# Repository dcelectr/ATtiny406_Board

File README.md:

# ATtiny406_Board
PCB Design Files for ATtiny406 Board

This board design is a variant of a board design that is found in the blog link below.

https://www.omzlo.com/articles/baremetal-programming-on-the-tinyavr-0-micro-controllers

The board features fairly easy to hand solder components, such as a SOIC20 IC and 0805 resistors, capacitors and LEDs, and it is breadboard friendly (100 mil spacing pin headers) with an orderly pin arrangement (PA0->PA7, PB0->PB5, and PC0->PC3). 

The programming connector is a standard FTDI USB-UART adapter pin-out. Since most FTDI USB-UART cables have different voltage for the Vcc and Vttl (such as the TTL-232R-3V3), a solder jumper (JP1) is open by default. The board can be powered from the breadboard pin headers or the FTDI programming header if the the jumper JP1 is closed. Using an FTDI TTL-232RG-VIP USB-UART requires the jumper JP1 to be closed so that the TTL-232RG-VIP adapter TTL voltage (Vttl) would be the same as the Vcc.

The Bill of Materials is also included (see file ATtiny406BOM.csv).

Resistance of 4k7 Ohms works reliably for programming the Attiny406 over the range of Vcc, from 5V to 3V3.

Programming was tested on Linux with updiprog https://github.com/DCelectronics/updiprog (which is written in C) instead of using pyupdi.

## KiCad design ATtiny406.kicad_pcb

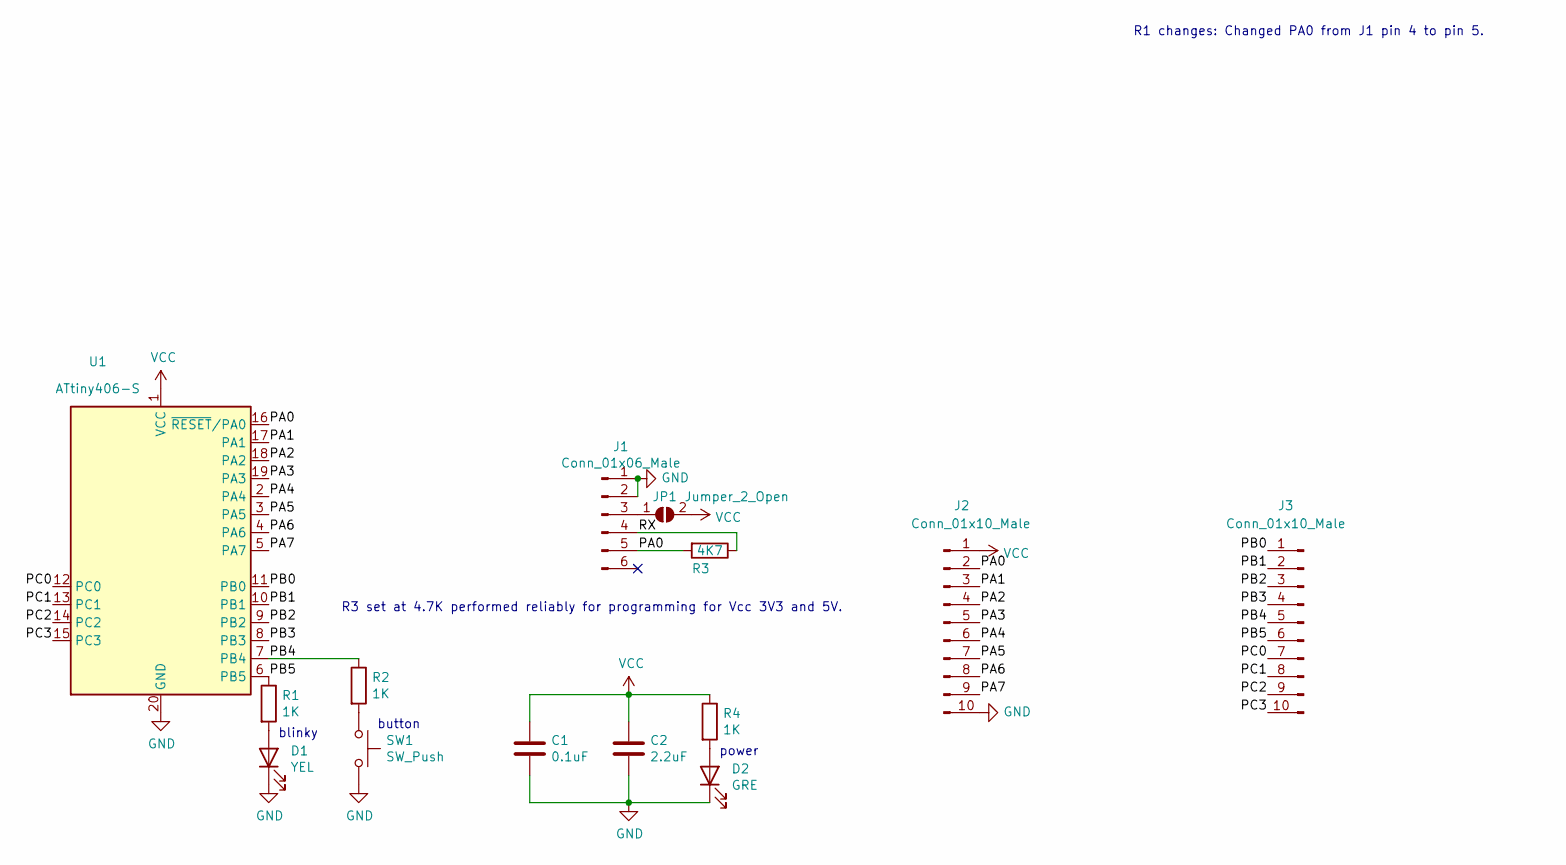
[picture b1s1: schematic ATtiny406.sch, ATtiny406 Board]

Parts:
C1: 0.1uF; C_0805_2012Metric_Pad1.18x1.45mm_HandSolder
C2: 2.2uF; C_0805_2012Metric_Pad1.18x1.45mm_HandSolder
D1: YEL; LED_0805_2012Metric_Pad1.15x1.40mm_HandSolder
D2: GRE; LED_0805_2012Metric_Pad1.15x1.40mm_HandSolder
J1: Conn_01x06_Male; PinHeader_1x06_P2.54mm_Vertical
J2, J3: Conn_01x10_Male; PinHeader_1x10_P2.54mm_Vertical
JP1: Jumper_2_Open; SolderJumper-2_P1.3mm_Open_RoundedPad1.0x1.5mm
R1, R2, R4: 1K; R_0805_2012Metric_Pad1.20x1.40mm_HandSolder
R3: 4K7; R_0805_2012Metric_Pad1.20x1.40mm_HandSolder
SW1: SW_Push; SW_SPST_B3U-1000P
U1: ATtiny406-S; SOIC-20W_7.5x12.8mm_P1.27mm

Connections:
/PA0: J1.5, J2.2, R3.2, U1.16 (~RESET~/PA0)
/PA1: J2.3, U1.17 (PA1)
/PA2: J2.4, U1.18 (PA2)
/PA3: J2.5, U1.19 (PA3)
/PA4: J2.6, U1.2 (PA4)
/PA5: J2.7, U1.3 (PA5)
/PA6: J2.8, U1.4 (PA6)
/PA7: J2.9, U1.5 (PA7)
/PB0: J3.1, U1.11 (PB0)
/PB1: J3.2, U1.10 (PB1)
/PB2: J3.3, U1.9 (PB2)
/PB3: J3.4, U1.8 (PB3)
/PB4: J3.5, R2.1, U1.7 (PB4)
/PB5: J3.6, R1.1, U1.6 (PB5)
/PC0: J3.7, U1.12 (PC0)
/PC1: J3.8, U1.13 (PC1)
/PC2: J3.9, U1.14 (PC2)
/PC3: J3.10, U1.15 (PC3)
/RX: J1.4, R3.1
GND: C1.2, C2.2, D1.1 (K), D2.1 (K), J1.1, J1.2, J2.10, SW1.2, U1.20 (GND)
unnamed: D1.2 (A), R1.2
unnamed: D2.2 (A), R4.2
unnamed: J1.3, JP1.1 (A)
unnamed: R2.2, SW1.1
VCC: C1.1, C2.1, J2.1, JP1.2 (B), R4.1, U1.1 (VCC)

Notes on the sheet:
power
blinky
button
R3 set at 4.7K performed reliably for programming for Vcc 3V3 and 5V.
R1 changes: Changed PA0 from J1 pin 4 to pin 5.

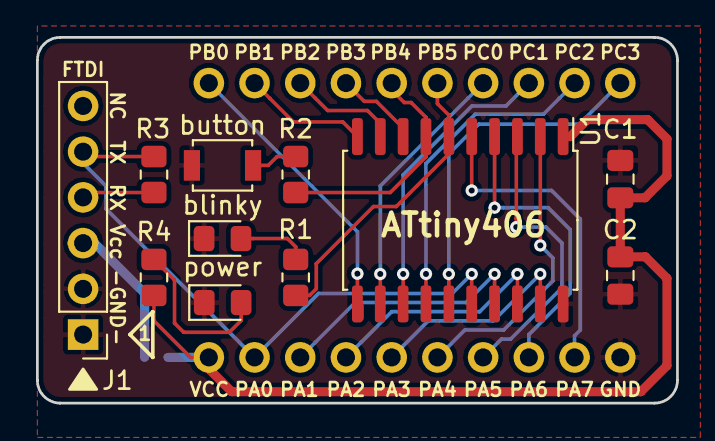
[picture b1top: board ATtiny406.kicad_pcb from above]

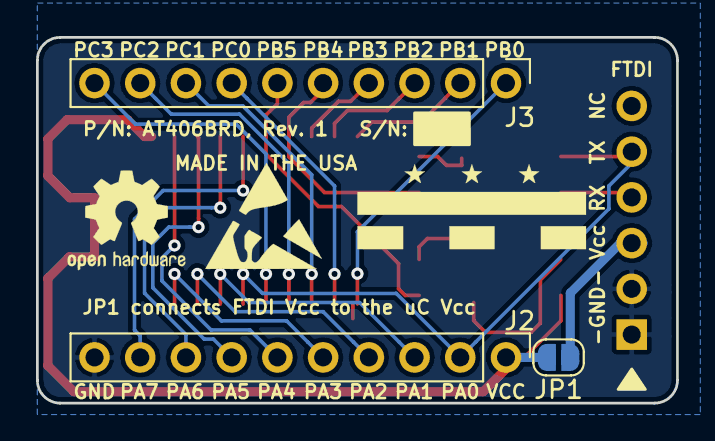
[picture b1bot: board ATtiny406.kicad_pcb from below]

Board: 2 copper layers, 35.6 x 20.3 mm, 14 parts (3 on the bottom side), 25 nets.

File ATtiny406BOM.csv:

Reference, Quantity, Value, Footprint, Datasheet, P/N
C1 ,1,"0.1uF","Capacitor_SMD:C_0805_2012Metric_Pad1.18x1.45mm_HandSolder","~","CC0805KRX7R7BB104"
C2 ,1,"2.2uF","Capacitor_SMD:C_0805_2012Metric_Pad1.18x1.45mm_HandSolder","~","CL21B225KOFNNNE"
D1 ,1,"YEL","LED_SMD:LED_0805_2012Metric_Pad1.15x1.40mm_HandSolder","~","150080YS75000"
D2 ,1,"GRE","LED_SMD:LED_0805_2012Metric_Pad1.15x1.40mm_HandSolder","~","150080VS75000"
J1 ,1,"Conn_01x06_Male","Connector_PinHeader_2.54mm:PinHeader_1x06_P2.54mm_Vertical","~","PH1-06-UA"
J2 J3 ,2,"Conn_01x10_Male","Connector_PinHeader_2.54mm:PinHeader_1x10_P2.54mm_Vertical","~","PH1-10-UA"
JP1 ,1,"Jumper_2_Open","Jumper:SolderJumper-2_P1.3mm_Open_RoundedPad1.0x1.5mm","~","N/A"
R1 R2 R4 ,3,"1K","Resistor_SMD:R_0805_2012Metric_Pad1.20x1.40mm_HandSolder","~","ERJ-6GEYJ102V"
R3 ,1,"4K7","Resistor_SMD:R_0805_2012Metric_Pad1.20x1.40mm_HandSolder","~","ERJ-6GEYJ472V"
SW1 ,1,"SW_Push","Button_Switch_SMD:SW_SPST_B3U-1000P","~","B3U-1000P"
U1 ,1,"ATtiny406-S","Package_SO:SOIC-20W_7.5x12.8mm_P1.27mm","http://ww1.microchip.com/downloads/en/DeviceDoc/Microchip%20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","ATTINY406-SFR"

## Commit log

2021-01-23 Revision 1 Release
    Revision 1 changes: Changed PA0 from J1 pin 4 to pin 5.
